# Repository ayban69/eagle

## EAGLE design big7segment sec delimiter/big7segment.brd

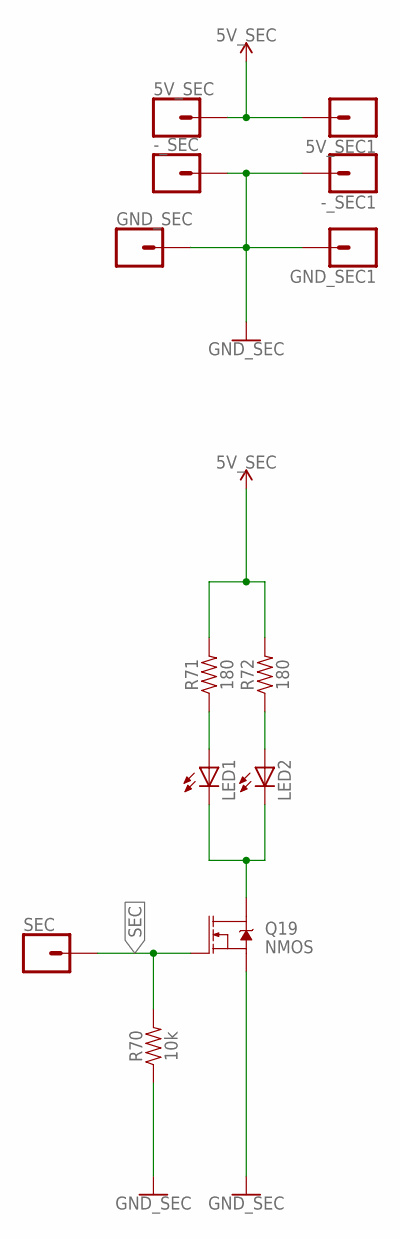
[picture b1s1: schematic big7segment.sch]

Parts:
5V_SEC, 5V_SEC1: CONN_01OFFSET; 1X01_OFFSET
-_SEC, -_SEC1: CONN_01OFFSET; 1X01_OFFSET
GND_SEC, GND_SEC1: CONN_01OFFSET; 1X01_OFFSET
LED1, LED2: LED5MM
Q19: NMOS; SOT23-3
R70: 10k; 0805
R71, R72: 180; 0805
SEC: CONN_01OFFSET; 1X01_OFFSET

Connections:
GND_SEC: -_SEC.1, -_SEC1.1, GND_SEC.1, GND_SEC1.1, Q19.2 (S), R70.1
unnamed: LED2.A, R72.1
unnamed: LED1.A, R71.1
unnamed: LED1.K (C), LED2.K (C), Q19.3 (D)
SEC: Q19.1 (G), R70.2, SEC.1
VCC_1: 5V_SEC.1, 5V_SEC1.1, R71.2, R72.2

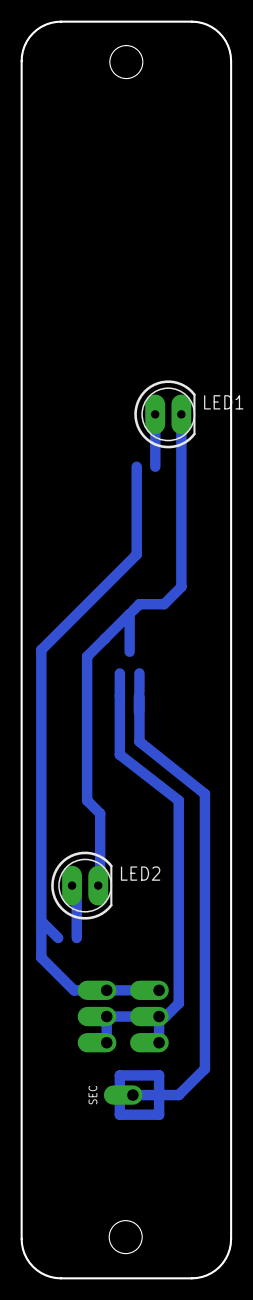
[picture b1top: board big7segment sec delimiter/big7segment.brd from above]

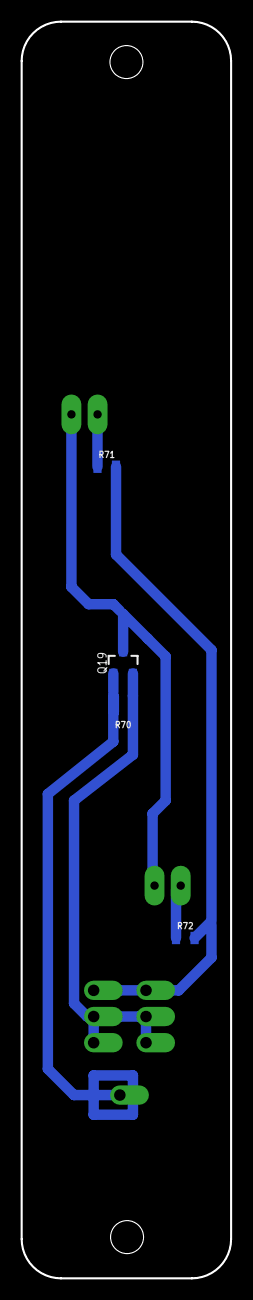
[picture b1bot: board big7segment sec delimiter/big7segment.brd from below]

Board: 2 copper layers, 20.3 x 121.9 mm, 13 parts (4 on the bottom side), 6 nets.

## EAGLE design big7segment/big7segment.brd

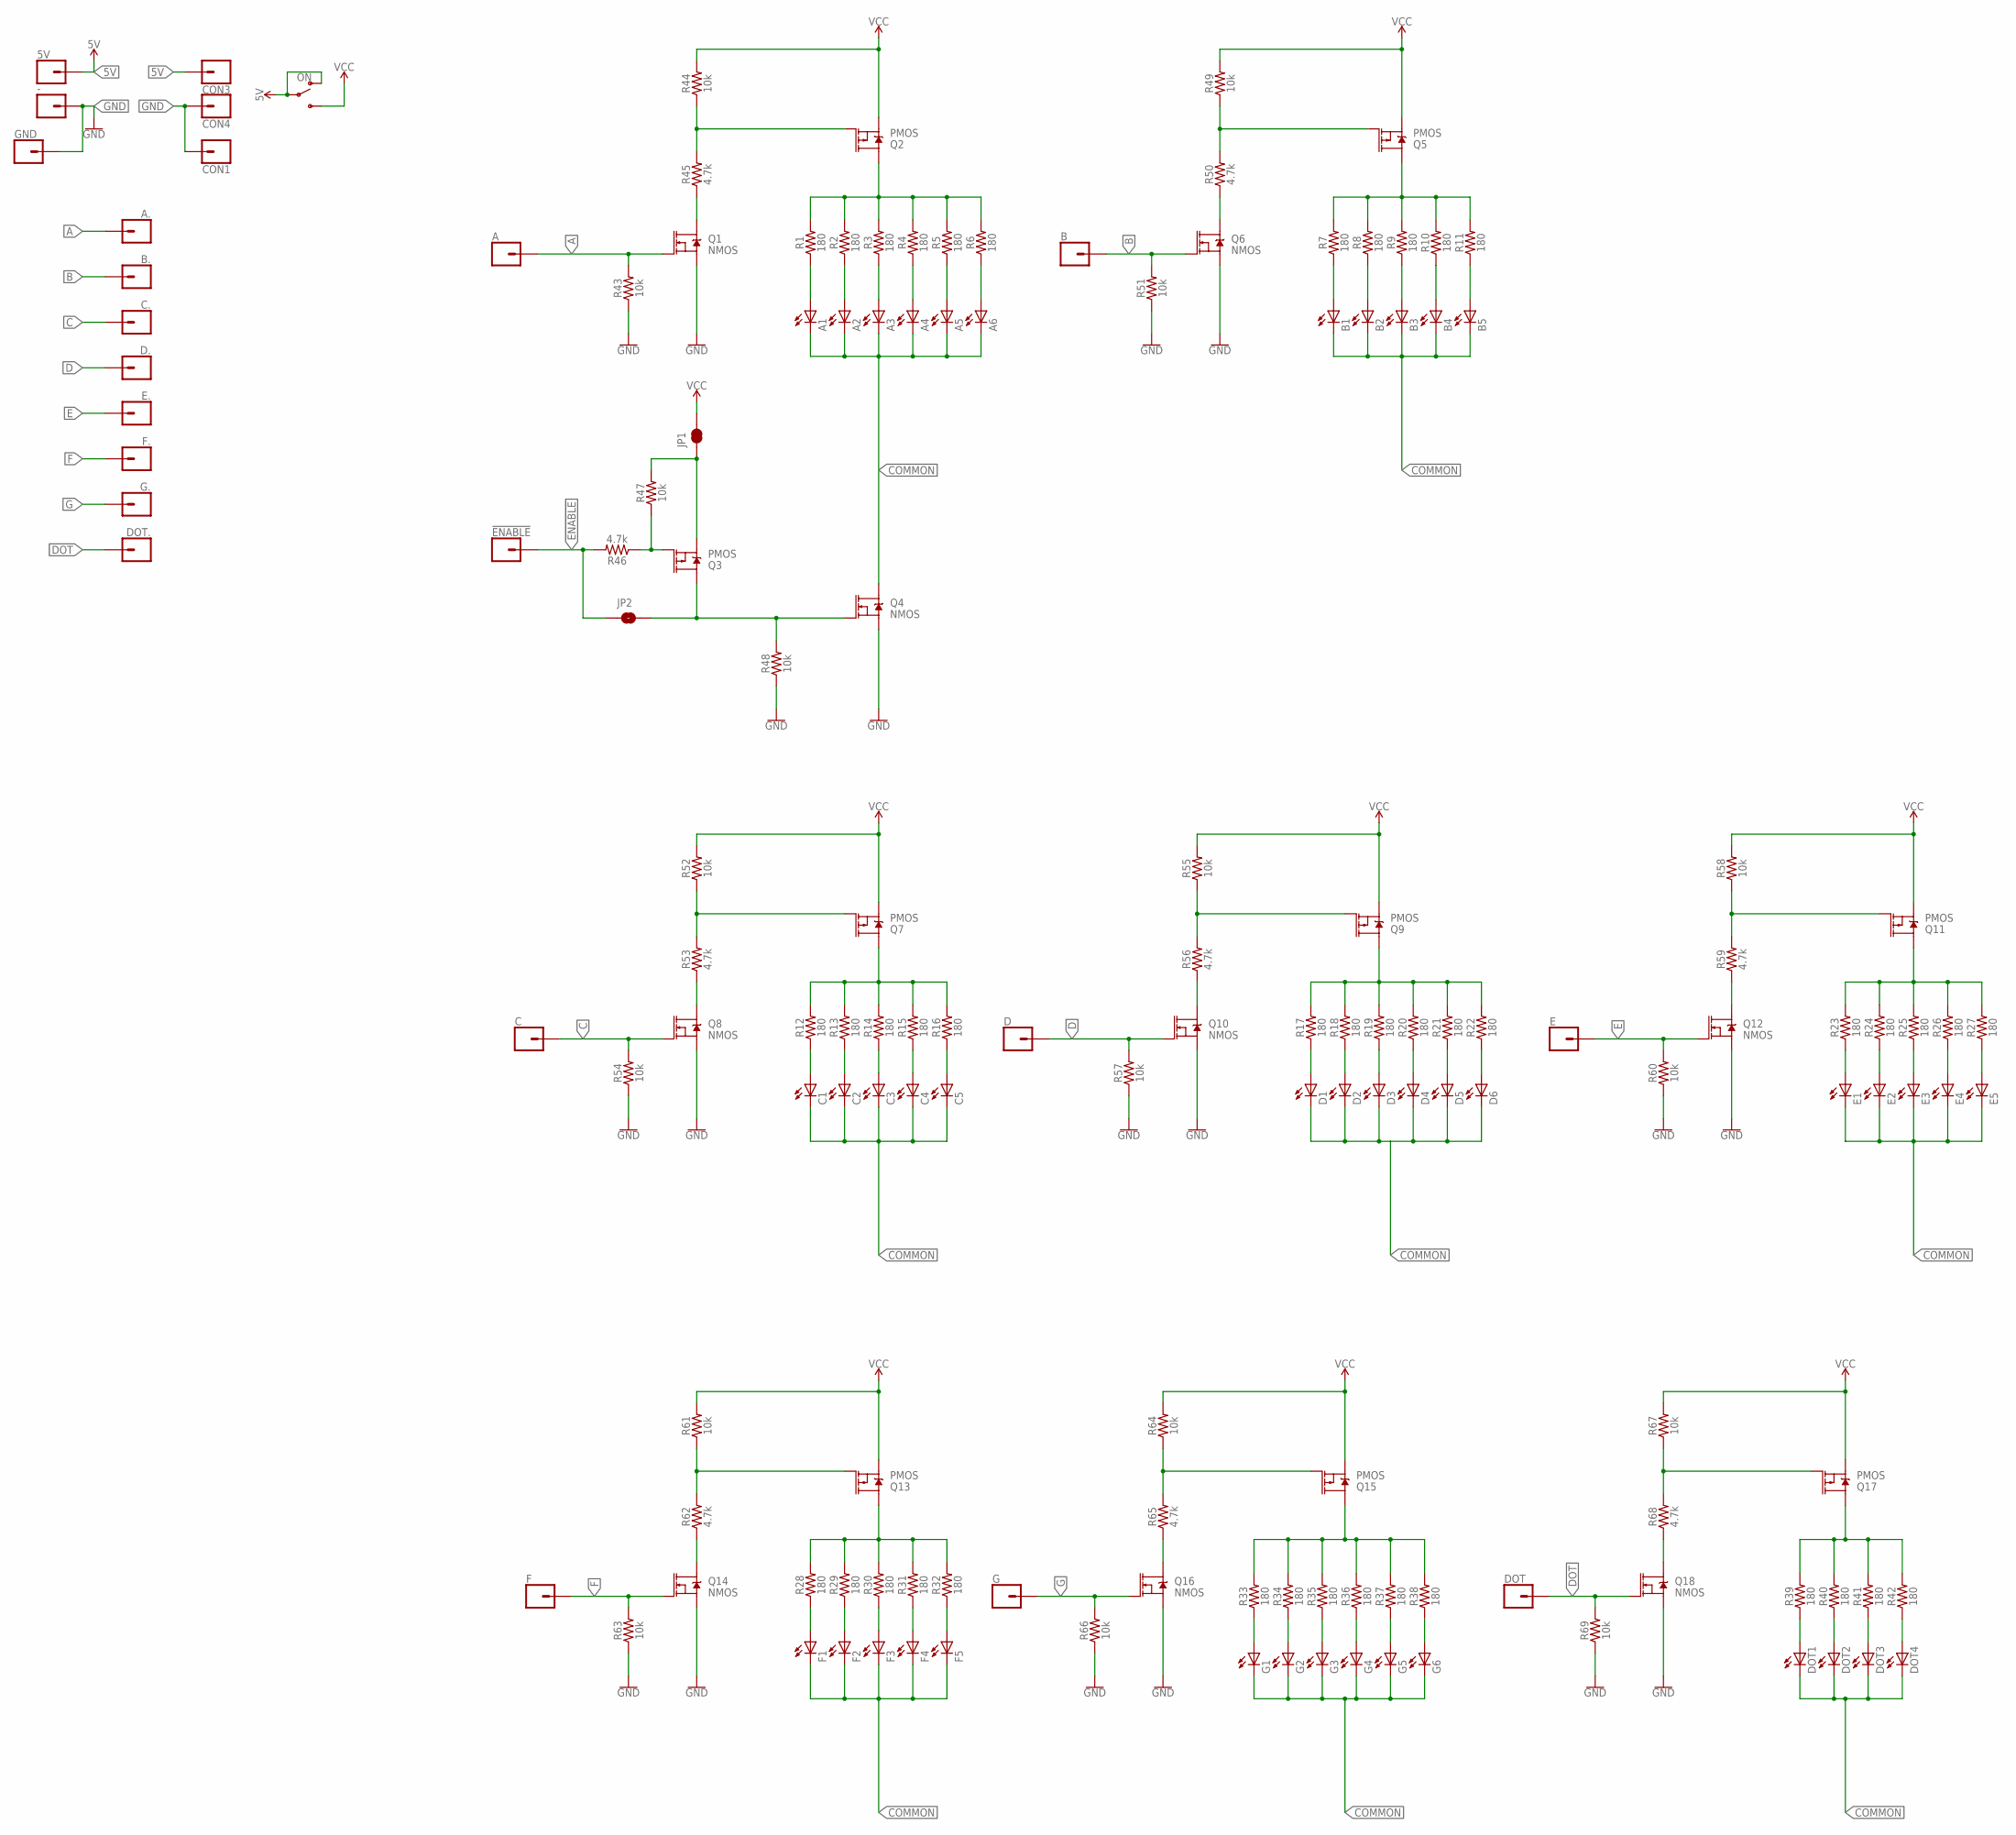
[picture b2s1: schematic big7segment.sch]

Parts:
5V: CONN_01OFFSET; 1X01_OFFSET
!ENABLE!: CONN_01OFFSET; 1X01_OFFSET
-: CONN_01OFFSET; 1X01_OFFSET
A, A.: CONN_01OFFSET; 1X01_OFFSET
A1, A2, A3, A4, A5, A6: LEDSML0805; SML0805
B, B.: CONN_01OFFSET; 1X01_OFFSET
B1, B2, B3, B4, B5: LEDSML0805; SML0805
C, C.: CONN_01OFFSET; 1X01_OFFSET
C1, C2, C3, C4, C5: LEDSML0805; SML0805
CON1, CON3, CON4: CONN_01OFFSET; 1X01_OFFSET
D, D.: CONN_01OFFSET; 1X01_OFFSET
D1, D2, D3, D4, D5, D6: LEDSML0805; SML0805
DOT, DOT.: CONN_01OFFSET; 1X01_OFFSET
DOT1, DOT2, DOT3, DOT4: LEDSML0805; SML0805
E, E.: CONN_01OFFSET; 1X01_OFFSET
E1, E2, E3, E4, E5: LEDSML0805; SML0805
F, F.: CONN_01OFFSET; 1X01_OFFSET
F1, F2, F3, F4, F5: LEDSML0805; SML0805
G, G.: CONN_01OFFSET; 1X01_OFFSET
G1, G2, G3, G4, G5, G6: LEDSML0805; SML0805
GND: CONN_01OFFSET; 1X01_OFFSET
JP1: JUMPER-SMT_2_NC_TRACE_NO-SILK; SMT-JUMPER_2_NC_TRACE_NO-SILK
JP2: JUMPER-SMT_2_NO_NO-SILK; SMT-JUMPER_2_NO_NO-SILK
ON: SWITCH-SPDT-PTH-11.6X4.0MM; SWITCH_SPDT_PTH_11.6X4.0MM
Q1, Q4, Q6, Q8, Q10, Q12, Q14, Q16, Q18: NMOS; SOT23-3
Q2, Q3, Q5, Q7, Q9, Q11, Q13, Q15, Q17: PMOS; SOT23-3
R1, R2, R3, R4, R5, R6, R7, R8, R9, R10, R11, R12, R13, R14, R15, R16, R17, R18, R19, R20, R21, R22, R23, R24, R25, R26, R27, R28, R29, R30, R31, R32, R33, R34, R35, R36, R37, R38, R39, R40, R41, R42: 180; 0805
R43, R44, R47, R48, R49, R51, R52, R54, R55, R57, R58, R60, R61, R63, R64, R66, R67, R69: 10k; 0805
R45, R46, R50, R53, R56, R59, R62, R65, R68: 4.7k; 0805

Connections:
5V: 5V.1, CON3.1, ON.1 (O), ON.2
!ENABLE!: !ENABLE!.1, JP2.1, R46.2
A: A.1, A..1, Q1.1 (G), R43.2
B: B.1, B..1, Q6.1 (G), R51.2
C: C.1, C..1, Q8.1 (G), R54.2
COMMON: A1.C, A2.C, A3.C, A4.C, A5.C, A6.C, B1.C, B2.C, B3.C, B4.C, B5.C, C1.C, C2.C, C3.C, C4.C, C5.C, D1.C, D2.C, D3.C, D4.C, D5.C, D6.C, DOT1.C, DOT2.C, DOT3.C, DOT4.C, E1.C, E2.C, E3.C, E4.C, E5.C, F1.C, F2.C, F3.C, F4.C, F5.C, G1.C, G2.C, G3.C, G4.C, G5.C, G6.C, Q4.3 (D)
D: D.1, D..1, Q10.1 (G), R57.2
DOT: DOT.1, DOT..1, Q18.1 (G), R69.2
E: E.1, E..1, Q12.1 (G), R60.2
F: F.1, F..1, Q14.1 (G), R63.2
G: G.1, G..1, Q16.1 (G), R66.2
GND: -.1, CON1.1, CON4.1, GND.1, Q1.2 (S), Q4.2 (S), Q6.2 (S), Q8.2 (S), Q10.2 (S), Q12.2 (S), Q14.2 (S), Q16.2 (S), Q18.2 (S), R43.1, R48.1, R51.1, R54.1, R57.1, R60.1, R63.1, R66.1, R69.1
unnamed: A1.A, R1.1
unnamed: A3.A, R3.1
unnamed: A4.A, R4.1
unnamed: A5.A, R5.1
unnamed: A6.A, R6.1
unnamed: A2.A, R2.1
unnamed: B1.A, R7.1
unnamed: B2.A, R8.1
unnamed: B3.A, R9.1
unnamed: B4.A, R10.1
unnamed: B5.A, R11.1
unnamed: C1.A, R12.1
unnamed: C2.A, R13.1
unnamed: C3.A, R14.1
unnamed: C4.A, R15.1
unnamed: C5.A, R16.1
unnamed: D1.A, R17.1
unnamed: D2.A, R18.1
unnamed: D3.A, R19.1
unnamed: D4.A, R20.1
unnamed: D5.A, R21.1
unnamed: D6.A, R22.1
unnamed: E1.A, R23.1
unnamed: E2.A, R24.1
unnamed: E3.A, R25.1
unnamed: E4.A, R26.1
unnamed: E5.A, R27.1
unnamed: F1.A, R28.1
unnamed: F2.A, R29.1
unnamed: F3.A, R30.1
unnamed: F4.A, R31.1
unnamed: F5.A, R32.1
unnamed: G1.A, R33.1
unnamed: G2.A, R34.1
unnamed: G3.A, R35.1
unnamed: G4.A, R36.1
unnamed: G5.A, R37.1
unnamed: G6.A, R38.1
unnamed: DOT1.A, R39.1
unnamed: DOT2.A, R40.1
unnamed: DOT3.A, R41.1
unnamed: DOT4.A, R42.1
unnamed: Q2.1 (G), R44.1, R45.2
unnamed: Q1.3 (D), R45.1
unnamed: Q5.1 (G), R49.1, R50.2
unnamed: Q2.3 (D), R1.2, R2.2, R3.2, R4.2, R5.2, R6.2
unnamed: Q3.1 (G), R46.1, R47.1
unnamed: JP2.2, Q3.3 (D), Q4.1 (G), R48.2
unnamed: Q5.3 (D), R7.2, R8.2, R9.2, R10.2, R11.2
unnamed: Q11.1 (G), R58.1, R59.2
unnamed: Q12.3 (D), R59.1
unnamed: Q6.3 (D), R50.1
unnamed: Q7.1 (G), R52.1, R53.2
unnamed: Q8.3 (D), R53.1
unnamed: Q7.3 (D), R12.2, R13.2, R14.2, R15.2, R16.2
unnamed: Q9.1 (G), R55.1, R56.2
unnamed: Q10.3 (D), R56.1
unnamed: Q9.3 (D), R17.2, R18.2, R19.2, R20.2, R21.2, R22.2
unnamed: Q13.3 (D), R28.2, R29.2, R30.2, R31.2, R32.2
unnamed: Q13.1 (G), R61.1, R62.2
unnamed: Q14.3 (D), R62.1
unnamed: Q15.3 (D), R33.2, R34.2, R35.2, R36.2, R37.2, R38.2
unnamed: Q15.1 (G), R64.1, R65.2
unnamed: Q16.3 (D), R65.1
unnamed: Q17.3 (D), R39.2, R40.2, R41.2, R42.2
unnamed: Q17.1 (G), R67.1, R68.2
unnamed: Q18.3 (D), R68.1
unnamed: JP1.1, Q3.2 (S), R47.2
unnamed: Q11.3 (D), R23.2, R24.2, R25.2, R26.2, R27.2
VCC: JP1.2, ON.3 (S), Q2.2 (S), Q5.2 (S), Q7.2 (S), Q9.2 (S), Q11.2 (S), Q13.2 (S), Q15.2 (S), Q17.2 (S), R44.2, R49.2, R52.2, R55.2, R58.2, R61.2, R64.2, R67.2

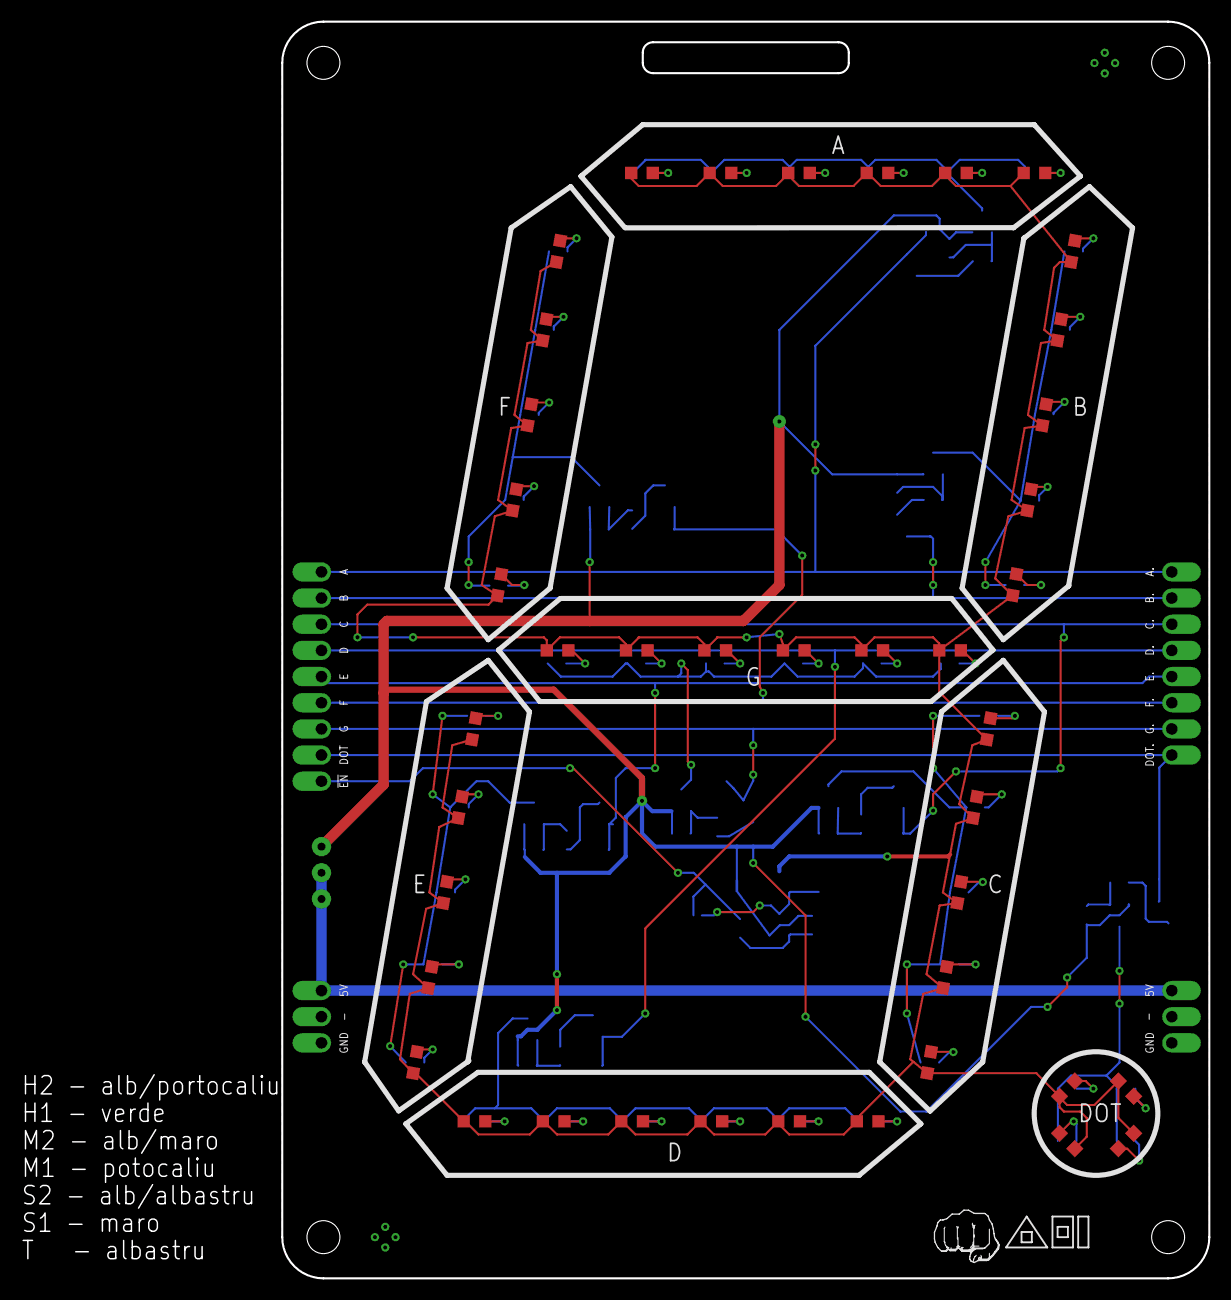
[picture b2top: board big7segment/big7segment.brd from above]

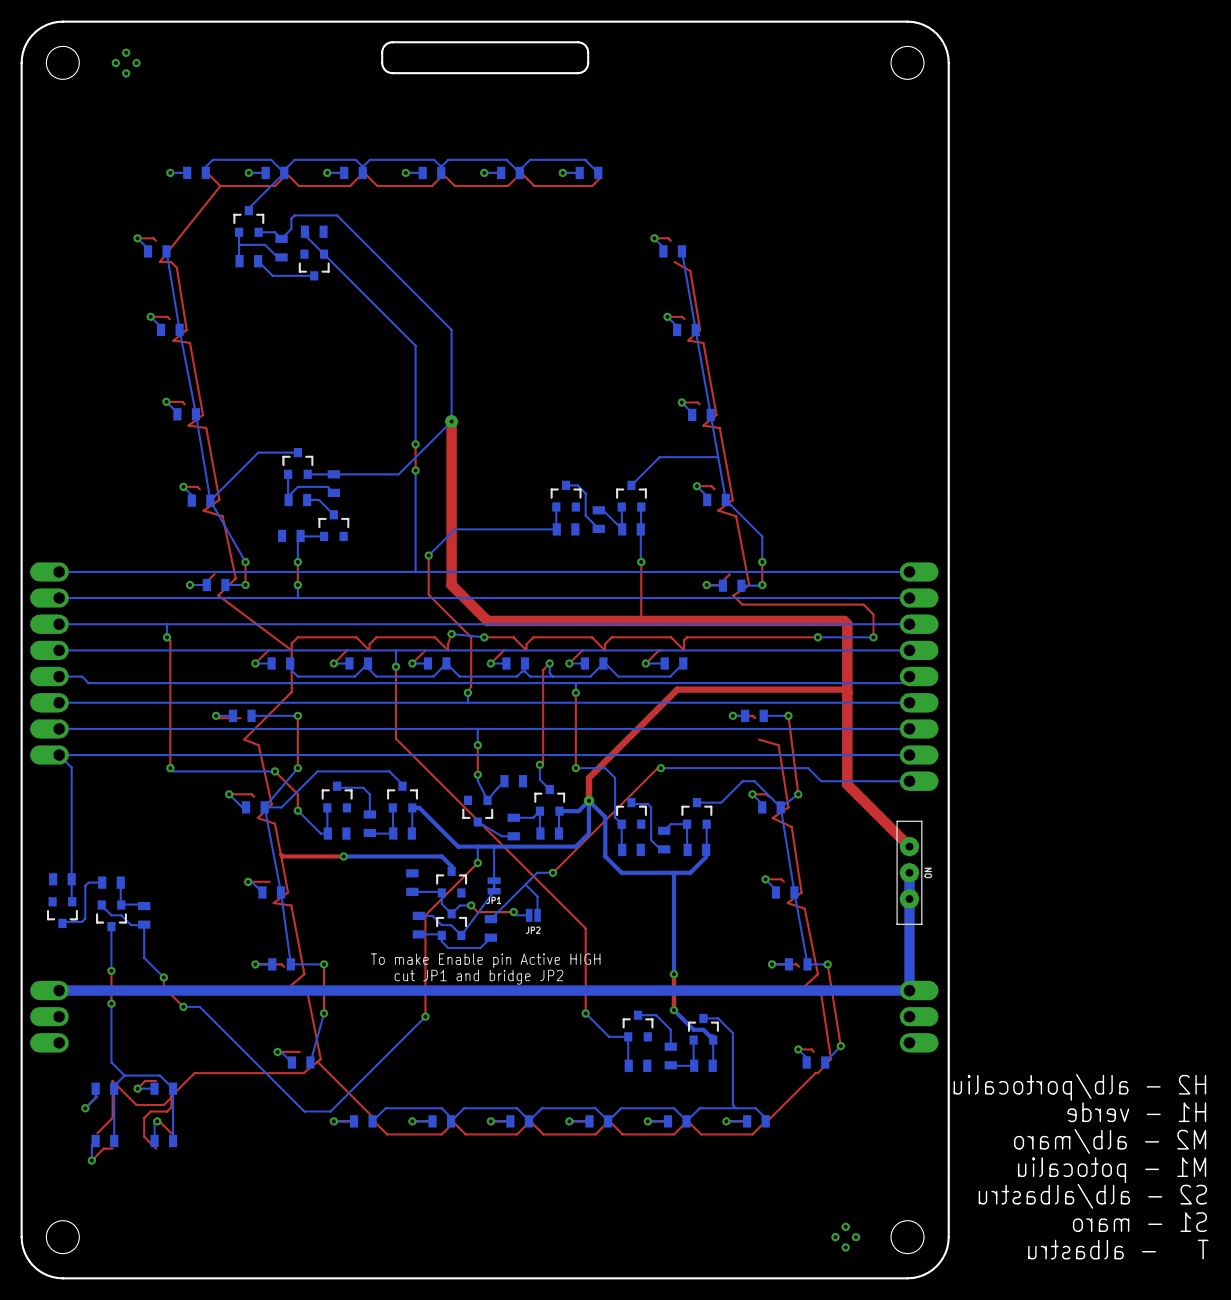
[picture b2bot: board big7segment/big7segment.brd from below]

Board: 2 copper layers, 115.3 x 122.0 mm, 156 parts (90 on the bottom side), 82 nets.

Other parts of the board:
U$1: ADILOGO

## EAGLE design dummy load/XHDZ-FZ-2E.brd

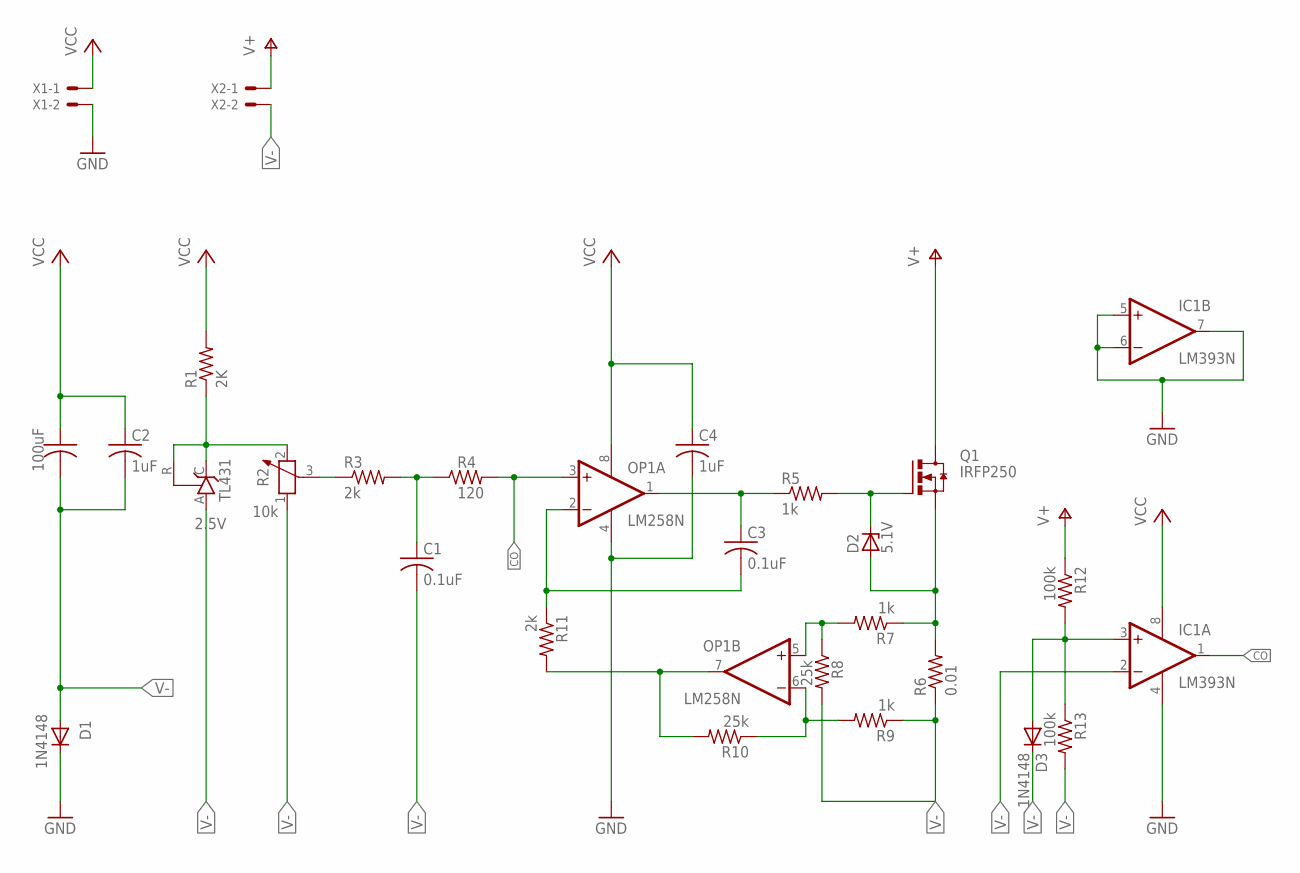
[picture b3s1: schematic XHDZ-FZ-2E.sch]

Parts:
25V: 100uF; C025-024X044
C1, C3: 0.1uF; C025-024X044
C2, C4: 1uF; C025-024X044
D1, D3: 1N4148; DO35-7
D2: 5.1V; C1702-15
IC1: LM393N; DIL08
OP1: LM258N; DIL08
Q1: IRFP250; TO-247AD-V
R1: 2K; 0207/5V
R2: 10k; PT-10
R3, R11: 2k; 0207/5V
R4: 120; 0207/5V
R5, R7, R9: 1k; 0207/5V
R6: 0.01; 0207/5V
R8, R10: 25k; 0207/5V
R12, R13: 100k; 0207/5V
TL431: 2.5V; TO92-CLP
X1, X2: 22-23-2021

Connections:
CO: IC1.1 (OUT), OP1.3 (+IN), R4.2
GND: C4.2, D1.C, IC1.4 (V-), IC1.5 (+IN), IC1.6 (-IN), IC1.7 (OUT), OP1.4 (V-), X1.2
unnamed: R1.1, R2.2, TL431.C, TL431.R
unnamed: D2.A, Q1.S, R6.2, R7.1
unnamed: R2.3, R3.1
unnamed: C1.1, R3.2, R4.1
unnamed: D3.A, IC1.3 (+IN), R12.2, R13.1
unnamed: C3.1, OP1.1 (OUT), R5.1
unnamed: C3.2, OP1.2 (-IN), R11.1
unnamed: D2.C, Q1.G, R5.2
unnamed: OP1.5 (+IN), R7.2, R8.1
unnamed: OP1.6 (-IN), R9.2, R10.1
unnamed: OP1.7 (OUT), R10.2, R11.2
V+: Q1.D, R12.1, X2.1
V-: 25V.2, C1.2, C2.2, D1.A, D3.C, IC1.2 (-IN), R2.1, R6.1, R8.2, R9.1, R13.2, TL431.A, X2.2
VCC: 25V.1, C2.1, C4.1, IC1.8 (V+), OP1.8 (V+), R1.2, X1.1

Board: 2 copper layers, 27 parts (0 on the bottom side), 16 nets, no tracks yet.

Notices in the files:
parts and their libraries:
SparkFun-Connectors: Licensing: Creative Commons ShareAlike 4.0 International - https://creativecommons.org/licenses/by-sa/4.0
usb connector: Copyright: Würth Elektronik
